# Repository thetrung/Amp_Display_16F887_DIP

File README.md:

# Amplifier Display with PIC16F887 (DIP Version)
The classic 8-bit **PIC16F887** will display all inputs on signals scan to its OLED (SSD1306) display. No LDO or any power-safe since we assume this will be powered by a stable current. Hope after like 5 Devkit version, this can be somewhat usable.

### Overview

### I/O Summpary
- I2C / UART / ICSP.
- 2-pins Power VCC/GND.
- Mini-USB-B (Power only).
- 1x Power & 1x (custom) LED.
- 1x Reset & 1x (custom) Mode Button.
- 14x Analog Inputs support.
- 14x Buttons support.

### Front View

### Back View

### Schematic

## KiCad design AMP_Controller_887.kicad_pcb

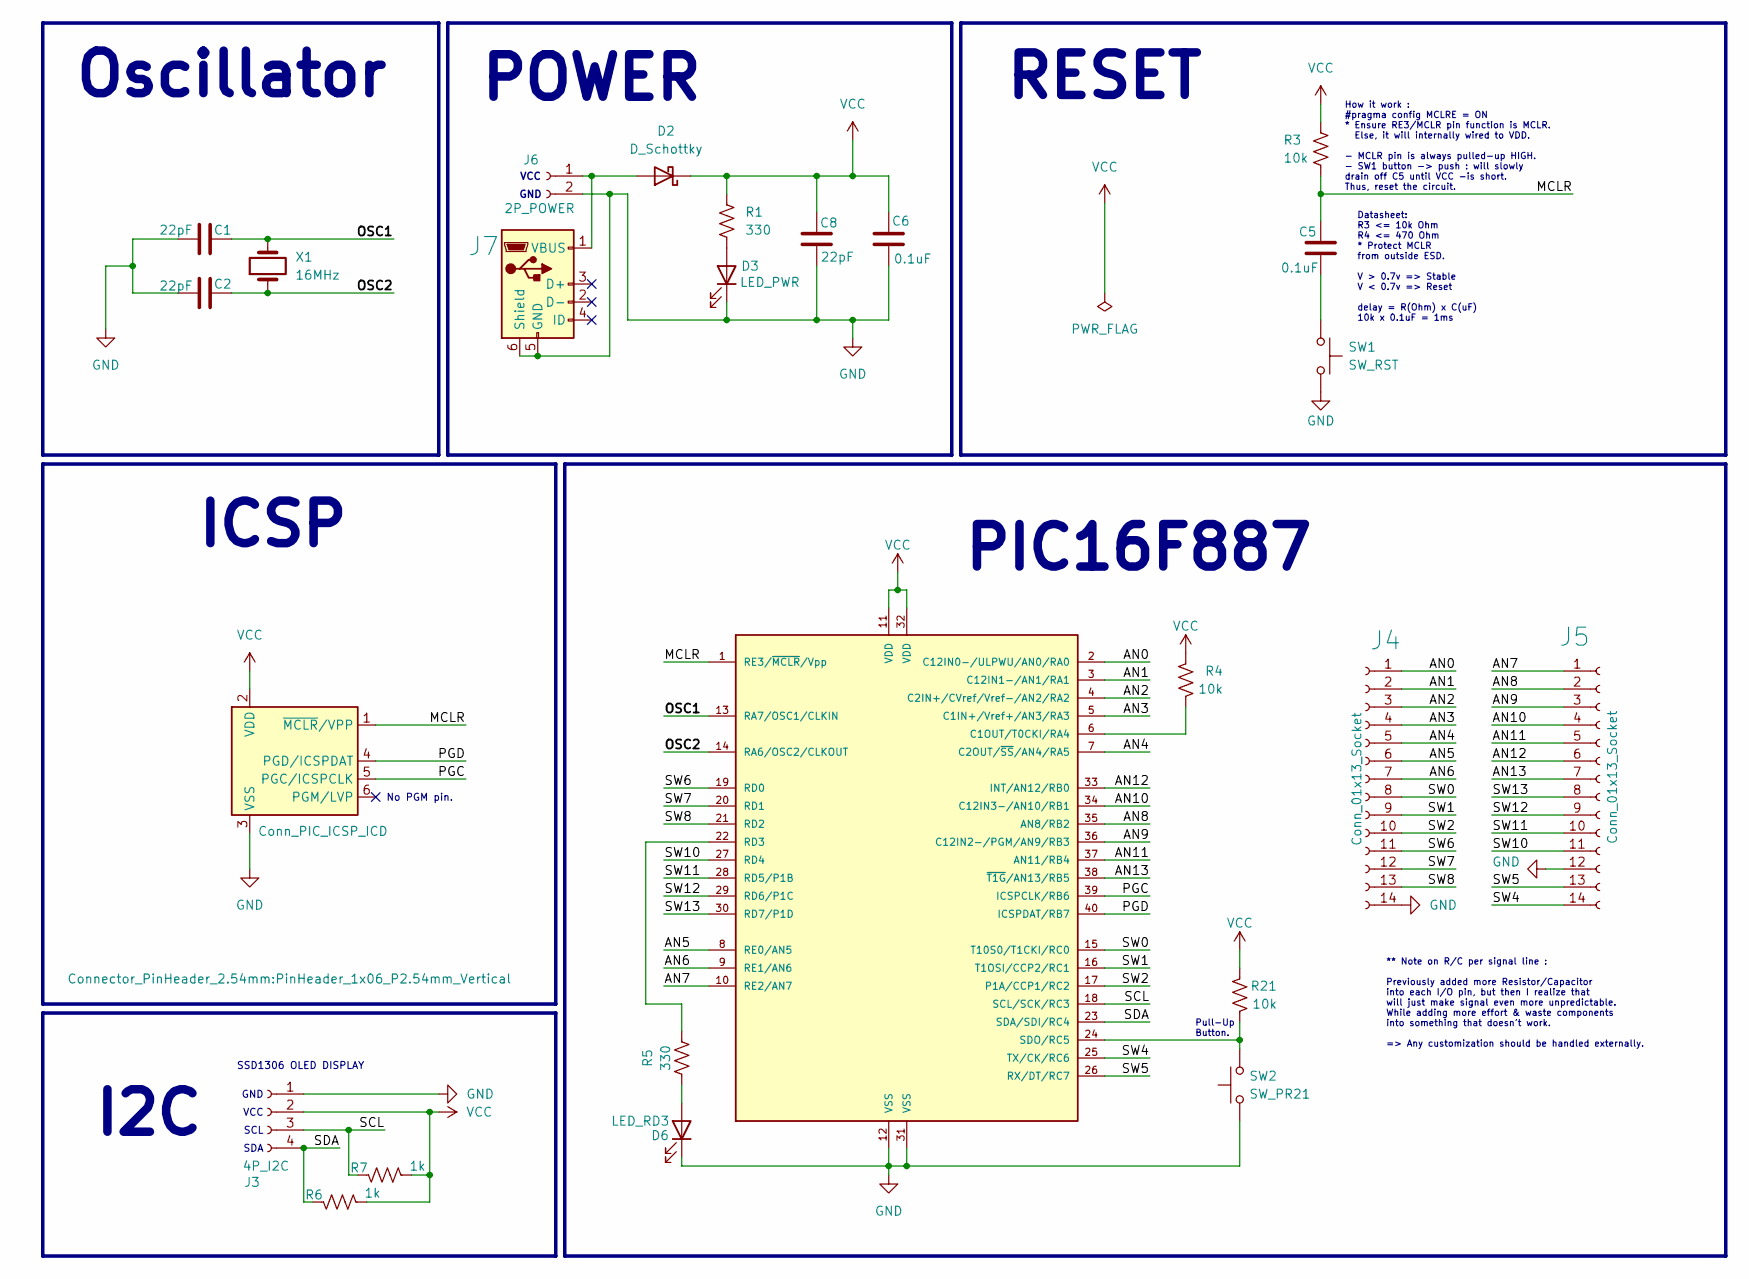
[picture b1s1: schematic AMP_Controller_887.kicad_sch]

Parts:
C1, C2, C8: 22pF; C_Disc_D3.0mm_W1.6mm_P2.50mm
C5, C6: 0.1uF; C_Disc_D3.0mm_W1.6mm_P2.50mm
D2: D_Schottky; D_DO-34_SOD68_P7.62mm_Horizontal
D3: LED_PWR; LED_D3.0mm_FlatTop
D6: LED_RD3; LED_D3.0mm_FlatTop
J1: Conn_PIC_ICSP_ICD; PinHeader_1x06_P2.54mm_Vertical
J3: 4P_I2C; PinSocket_1x04_P2.54mm_Vertical
J4, J5: Conn_01x13_Socket; PinSocket_1x14_P2.54mm_Vertical
J6: 2P_POWER; PinSocket_1x02_P2.54mm_Vertical
J7: USB_Mini_B_90_Angled; USB_MINI_B_90_Angled
PIC16F887: PIC16F887-I/P; DIP-40_W15.24mm
R1, R5: 330; R_Axial_DIN0204_L3.6mm_D1.6mm_P5.08mm_Horizontal
R3, R4, R21: 10k; R_Axial_DIN0204_L3.6mm_D1.6mm_P5.08mm_Horizontal
R6, R7: 1k; R_Axial_DIN0204_L3.6mm_D1.6mm_P5.08mm_Horizontal
SW1: SW_RST; SW_PUSH_6mm
SW2: SW_PR21; SW_PUSH_6mm
X1: 16MHz; Crystal_HC49-4H_Vertical

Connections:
/AN0: J4.1, PIC16F887.2 (C12IN0-/ULPWU/AN0/RA0)
/AN1: J4.2, PIC16F887.3 (C12IN1-/AN1/RA1)
/AN2: J4.3, PIC16F887.4 (C2IN+/CVref/Vref-/AN2/RA2)
/AN3: J4.4, PIC16F887.5 (C1IN+/Vref+/AN3/RA3)
/AN4: J4.5, PIC16F887.7 (C2OUT/~SS/AN4/RA5)
/AN5: J4.6, PIC16F887.8 (RE0/AN5)
/AN6: J4.7, PIC16F887.9 (RE1/AN6)
/AN7: J5.1, PIC16F887.10 (RE2/AN7)
/AN8: J5.2, PIC16F887.35 (AN8/RB2)
/AN9: J5.3, PIC16F887.36 (C12IN2-/PGM/AN9/RB3)
/AN10: J5.4, PIC16F887.34 (C12IN3-/AN10/RB1)
/AN11: J5.5, PIC16F887.37 (AN11/RB4)
/AN12: J5.6, PIC16F887.33 (INT/AN12/RB0)
/AN13: J5.7, PIC16F887.38 (~T1G/AN13/RB5)
/MCLR: C5.2, J1.1 (~MCLR/VPP), PIC16F887.1 (RE3/~MCLR/Vpp), R3.2
/OSC1: C1.1, PIC16F887.13 (RA7/OSC1/CLKIN), X1.2
/OSC2: C2.1, PIC16F887.14 (RA6/OSC2/CLKOUT), X1.1
/PGC: J1.5 (PGC/ICSPCLK), PIC16F887.39 (ICSPCLK/RB6)
/PGD: J1.4 (PGD/ICSPDAT), PIC16F887.40 (ICSPDAT/RB7)
/SCL: J3.3, PIC16F887.18 (SCL/SCK/RC3), R7.1
/SDA: J3.4, PIC16F887.23 (SDA/SDI/RC4), R6.1
/SW0: J4.8, PIC16F887.15 (T10S0/T1CKI/RC0)
/SW1: J4.9, PIC16F887.16 (T1OSI/CCP2/RC1)
/SW2: J4.10, PIC16F887.17 (P1A/CCP1/RC2)
/SW4: J5.14, PIC16F887.25 (TX/CK/RC6)
/SW5: J5.13, PIC16F887.26 (RX/DT/RC7)
/SW6: J4.11, PIC16F887.19 (RD0)
/SW7: J4.12, PIC16F887.20 (RD1)
/SW8: J4.13, PIC16F887.21 (RD2)
/SW10: J5.11, PIC16F887.27 (RD4)
/SW11: J5.10, PIC16F887.28 (RD5/P1B)
/SW12: J5.9, PIC16F887.29 (RD6/P1C)
/SW13: J5.8, PIC16F887.30 (RD7/P1D)
GND: C1.2, C2.2, C6.1, C8.2, D3.1 (K), D6.1 (K), J1.3 (VSS), J3.1, J4.14, J5.12, J6.2, J7.5 (GND), J7.6 (Shield), PIC16F887.12 (VSS), PIC16F887.31 (VSS), SW1.2, SW2.1
unnamed: C5.1, SW1.1
unnamed: D2.2 (A), J6.1, J7.1 (VBUS)
unnamed: D3.2 (A), R1.2
unnamed: D6.2 (A), R5.1
unnamed: PIC16F887.6 (C1OUT/T0CKI/RA4), R4.2
unnamed: PIC16F887.22 (RD3), R5.2
unnamed: PIC16F887.24 (SDO/RC5), R21.2, SW2.2
VCC: C6.2, C8.1, D2.1 (K), J1.2 (VDD), J3.2, PIC16F887.11 (VDD), PIC16F887.32 (VDD), R1.1, R3.1, R4.1, R6.2, R7.2, R21.1

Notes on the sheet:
RESET
POWER
ICSP
** Note on R/C per signal line : Previously added more Resistor/Capacitor into each I/O pin, but then I realize that will just make signal even more unpredictable. While adding more effort & waste components into something that doesn't work. => Any customization should be handled externally.
VCC
How it work : #pragma config MCLRE = ON * Ensure RE3/MCLR pin function is MCLR. Else, it will internally wired to VDD. - MCLR pin is always pulled-up HIGH. - SW1 button -> push : will slowly drain off C5 until VCC -is short. Thus, reset the circuit.
Pull-Up Button.
SDA
GND
I2C
Datasheet: R3 <= 10k Ohm R4 <= 470 Ohm * Protect MCLR from outside ESD. V > 0.7v => Stable V < 0.7v => Reset delay = R(Ohm) x C(uF) 10k x 0.1uF = 1ms
SCL
SSD1306 OLED DISPLAY
Oscillator
No PGM pin.
PIC16F887

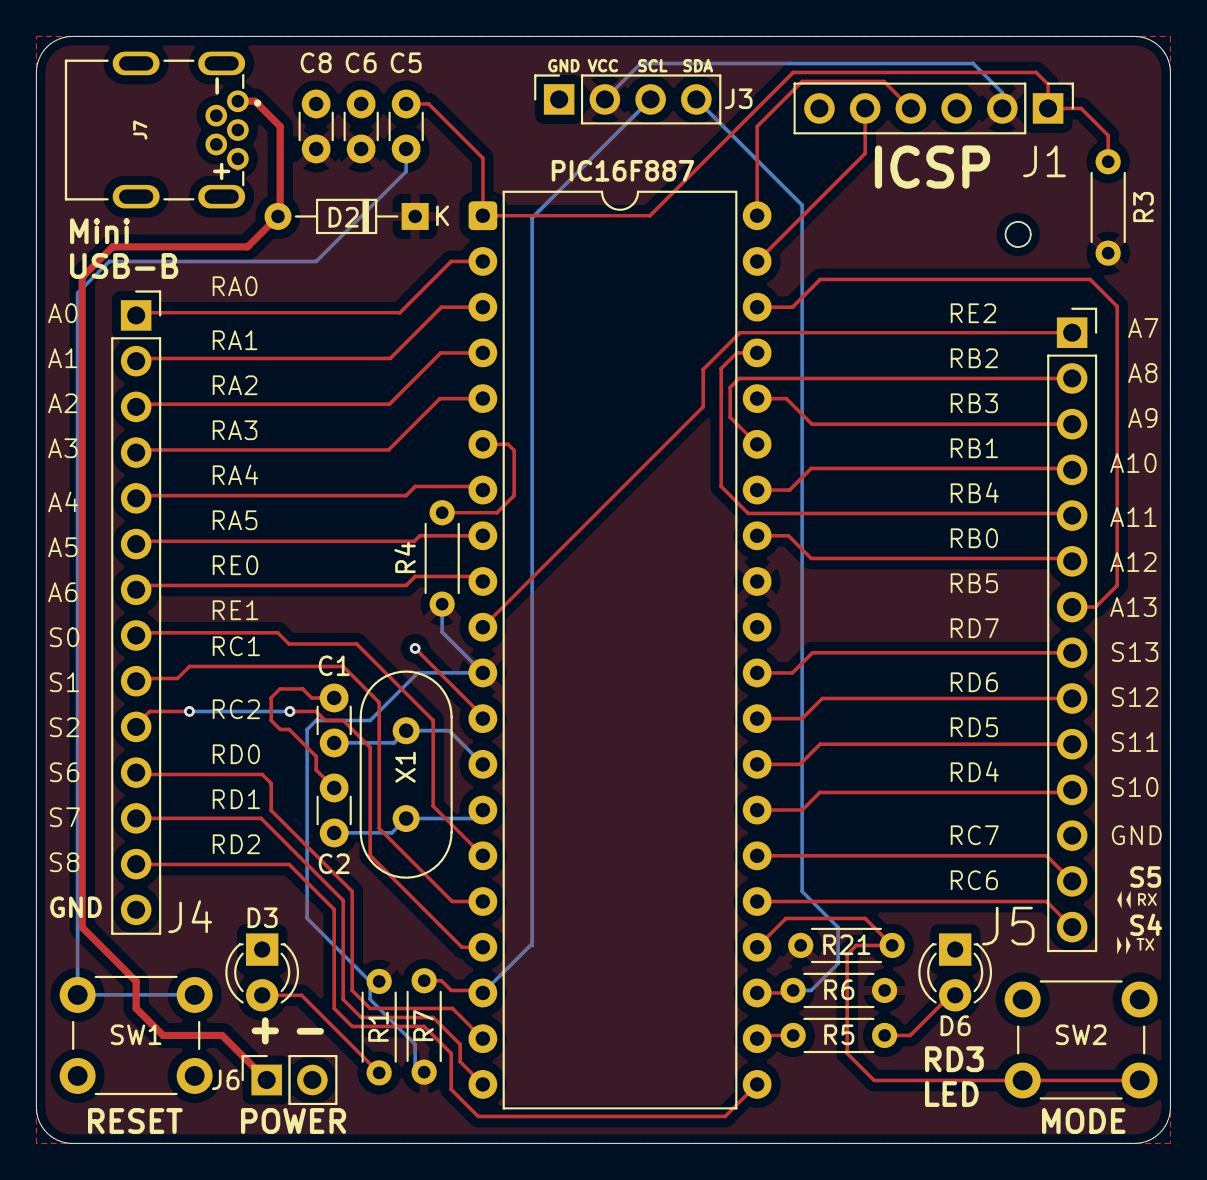
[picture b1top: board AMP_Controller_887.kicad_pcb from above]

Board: 2 copper layers, 63.0 x 61.5 mm, 25 parts (0 on the bottom side), 42 nets.

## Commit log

2025-04-16 Refined Schematic + Sketch Layout
2025-04-17 Finished layout.
2025-04-17 Fix power pins position to not block OLED display.
2025-04-19 Swap position of S5/S4 (aka: RX/TX) downward
2025-04-30 Rev.2 : Flip USB to be normal, remove all R/C from I/O, Fix pull-up button, refine fonts.
2025-05-14 Update name
